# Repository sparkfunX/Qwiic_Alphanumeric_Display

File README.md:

SparkX Qwiic Alphanumeric Display
========================================

[*Alphanumeric Display (Qwiic) (SPX-)*]()

The SparkFun Qwiic Alphanumeric Display is a 14-segment, 4 digit alphanumeric display with the Holtek HT16K33 LED Driver that allows you for control every segment individually through an I2C bus. 

Repository Contents
-------------------

* **/Documents** - Data sheet for the LED Driver and Alphanumeric Displays (Blue and Red)
* **/Hardware** - Eagle design files (.brd, .sch)
* **/Production** - Production panel files (.brd) within the Production folder

License Information
-------------------

This product is _**open source**_! 

Please review the LICENSE.md file for license information. 

If you have any questions or concerns on licensing, please contact technical support on our [SparkFun forums](https://forum.sparkfun.com/viewforum.php?f=152).

Distributed as-is; no warranty is given.

- Your friends at SparkFun.

_<COLLABORATION CREDIT>_

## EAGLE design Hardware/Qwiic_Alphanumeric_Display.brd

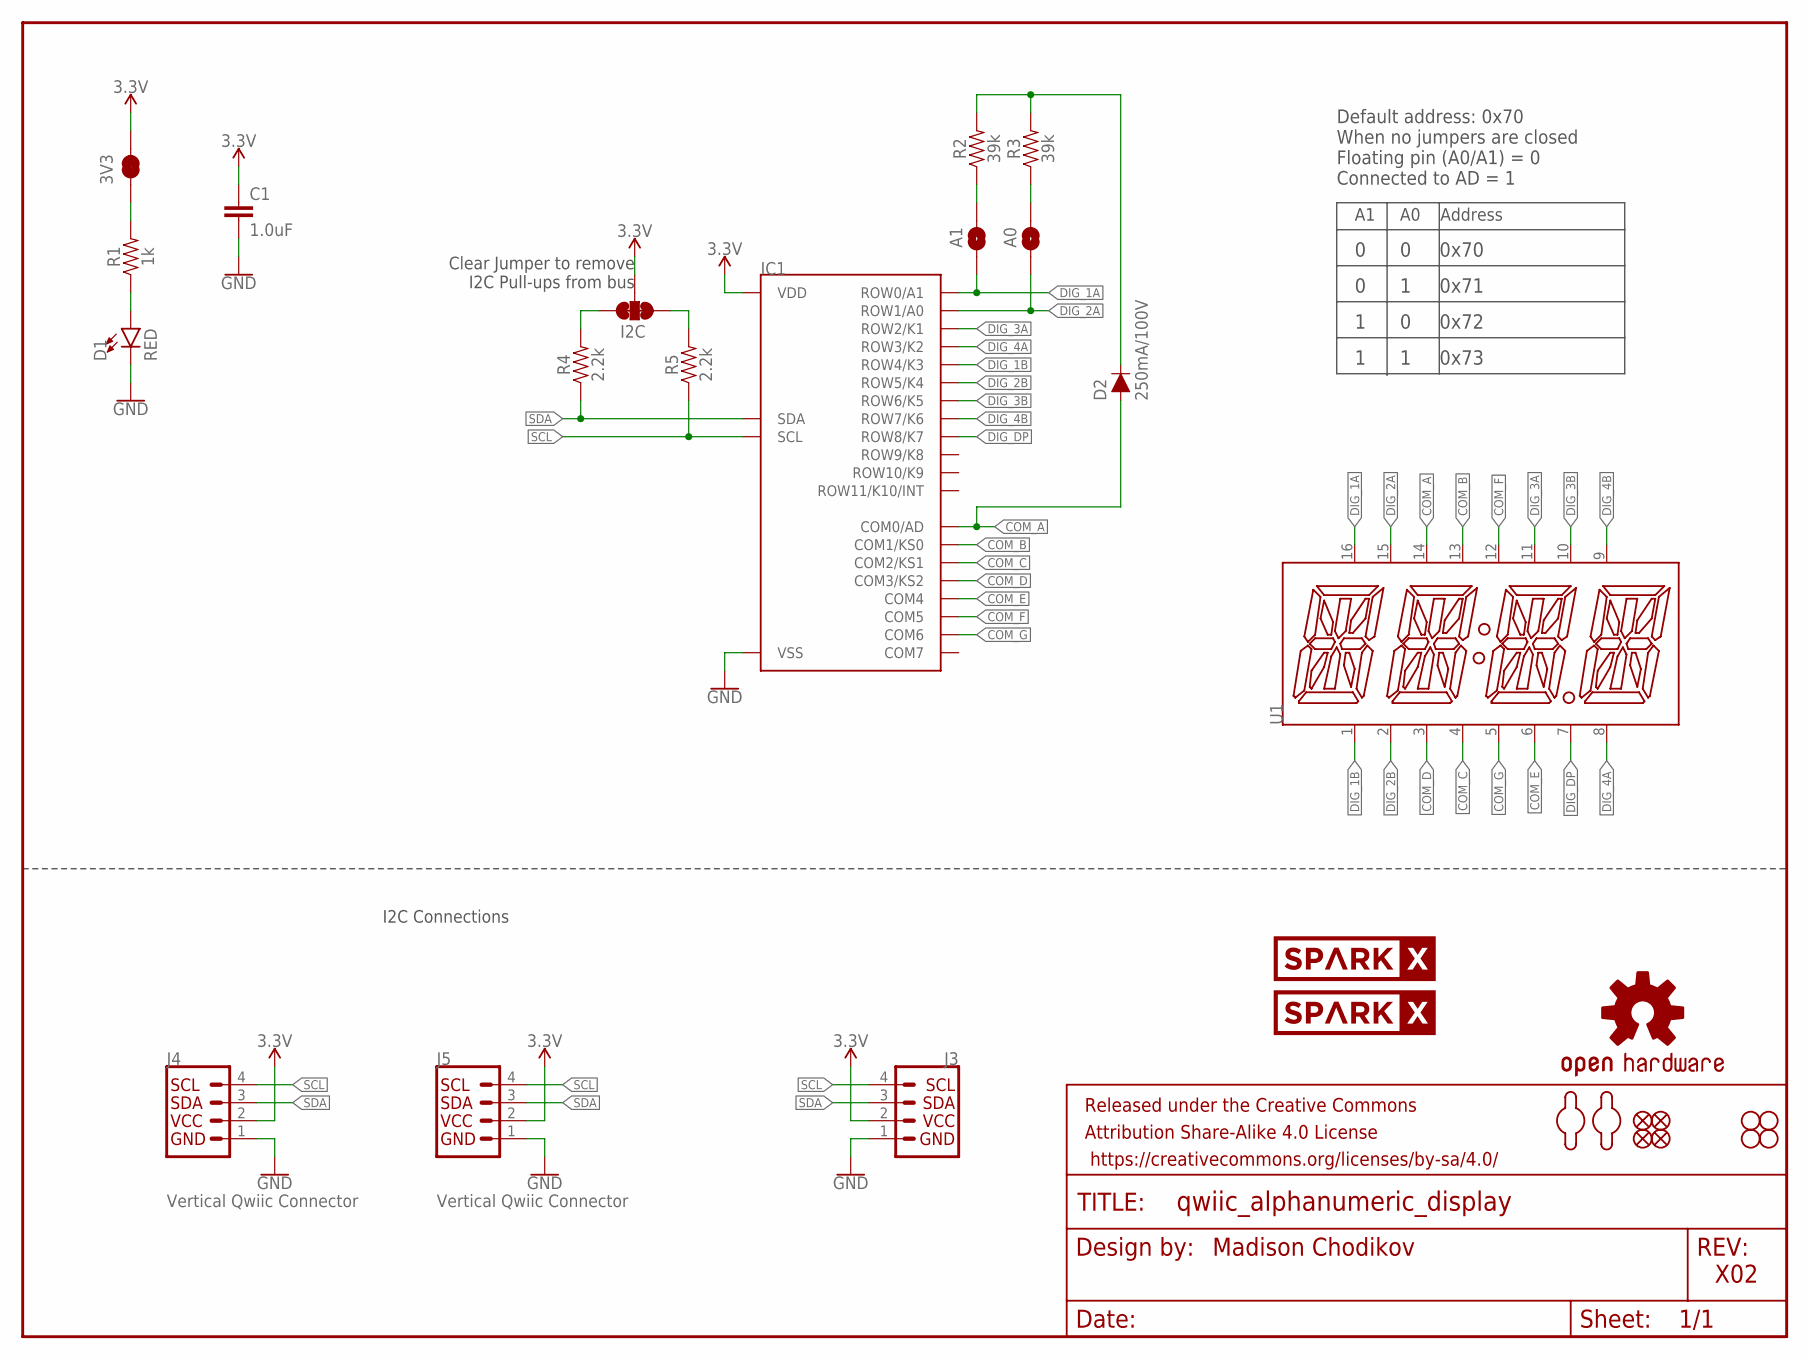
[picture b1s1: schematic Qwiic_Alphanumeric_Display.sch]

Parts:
3V3: JUMPER-SMT_2_NC_TRACE_SILK; SMT-JUMPER_2_NC_TRACE_SILK
A0, A1: JUMPER-SMT_2_NO_SILK; SMT-JUMPER_2_NO_SILK
C1: 1.0uF; 0603
D1: RED; LED-0603
D2: 250mA/100V; SOD-323
FD1, FD2, FD3, FD4: FIDUCIAL1X2; FIDUCIAL-1X2
FRAME1: FRAME-LETTER; CREATIVE_COMMONS
H1, H2, H3, H4: STAND-OFF
I2C: JUMPER-SMT_3_2-NC_TRACE_SILK; SMT-JUMPER_3_2-NC_TRACE_SILK
IC1: HT16K33
J3: I2C_STANDARD_NO_SILK; 1X04_NO_SILK
J4, J5: Vertical Qwiic Connector; JST04_1MM_VERT
LOGO1: OSHW-LOGOMINI; OSHW-LOGO-MINI
R1: 1k; 0603
R2, R3: 39k; 0603
R4, R5: 2.2k; 0603
U1: SILSMART_DISPLAY
U$7, U$8: SPARKX-LOGO4; SPARKX-MEDIUM
U$18, U$19: MOUNTING_HOLE_M2-0.4X6

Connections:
3.3V: 3V3.2, C1.1, I2C.2, IC1.24 (VDD), J3.2, J4.2, J5.2
COM_A: D2.A, IC1.2 (COM0/AD), U1.14 (COM_A)
COM_B: IC1.3 (COM1/KS0), U1.13 (COM_B)
COM_C: IC1.4 (COM2/KS1), U1.4 (COM_C)
COM_D: IC1.5 (COM3/KS2), U1.3 (COM_D)
COM_E: IC1.6 (COM4), U1.6 (COM_E)
COM_F: IC1.7 (COM5), U1.12 (COM_F)
COM_G: IC1.8 (COM6), U1.5 (COM_G1)
DIG_1A: A1.1, IC1.21 (ROW0/A1), U1.16 (DIG_1A)
DIG_1B: IC1.17 (ROW4/K3), U1.1 (DIG_1B)
DIG_2A: A0.1, IC1.20 (ROW1/A0), U1.15 (DIG_2A)
DIG_2B: IC1.16 (ROW5/K4), U1.2 (DIG_2B)
DIG_3A: IC1.19 (ROW2/K1), U1.11 (DIG_3A)
DIG_3B: IC1.15 (ROW6/K5), U1.10 (DIG_3B)
DIG_4A: IC1.18 (ROW3/K2), U1.8 (DIG_4A)
DIG_4B: IC1.14 (ROW7/K6), U1.9 (DIG_4B)
DIG_DP: IC1.13 (ROW8/K7), U1.7 (DIG_DP)
GND: C1.2, D1.C, IC1.1 (VSS), J3.1, J4.1, J5.1
unnamed: D1.A, R1.1
unnamed: A1.2, R2.1
unnamed: A0.2, R3.1
unnamed: I2C.1, R5.2
unnamed: I2C.3, R4.2
unnamed: D2.C, R2.2, R3.2
unnamed: 3V3.1, R1.2
SCL: IC1.22 (SCL), J3.4, J4.4, J5.4, R5.1
SDA: IC1.23 (SDA), J3.3, J4.3, J5.3, R4.1

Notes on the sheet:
Madison Chodikov
I2C Connections
Clear Jumper to remove I2C Pull-ups from bus
A1 A0 Address
0 0 0x70
0 1 0x71
1 0 0x72
1 1 0x73
Default address: 0x70 When no jumpers are closed Floating pin (A0/A1) = 0 Connected to AD = 1
X02

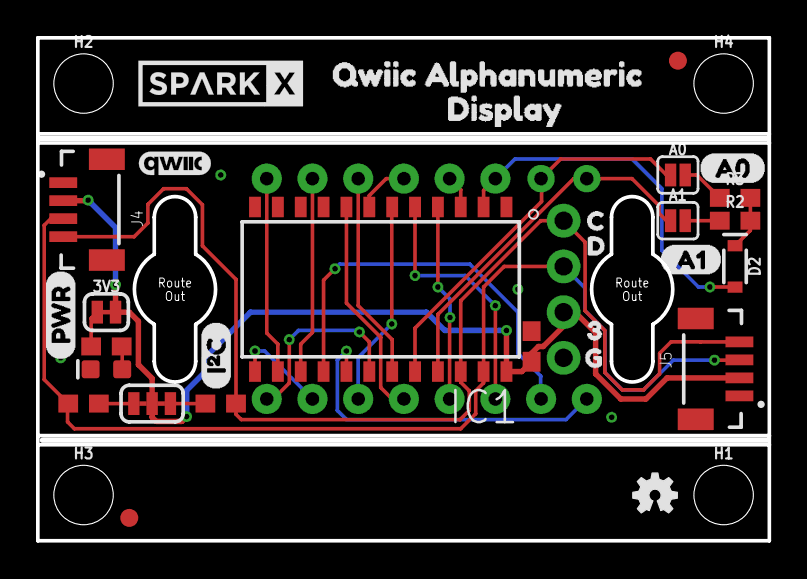
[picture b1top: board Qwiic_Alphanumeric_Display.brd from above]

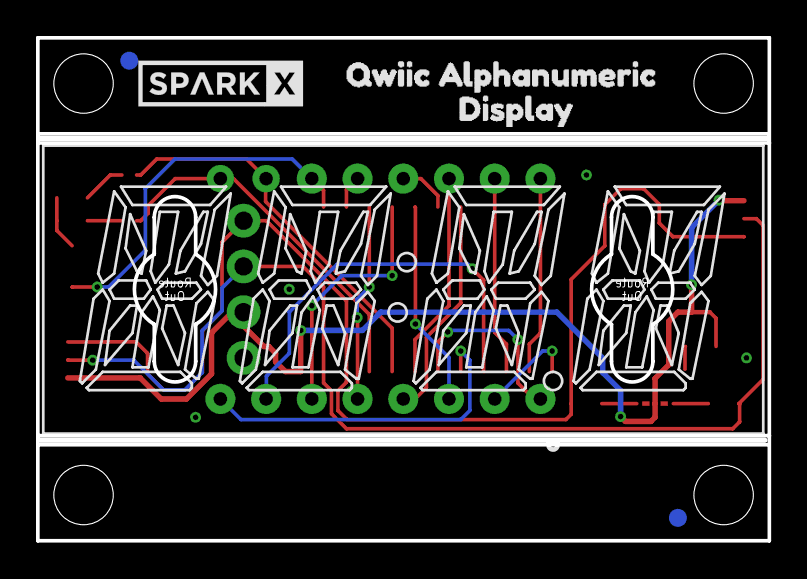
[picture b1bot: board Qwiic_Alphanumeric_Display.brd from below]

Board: 2 copper layers, 40.6 x 27.9 mm, 44 parts (6 on the bottom side), 27 nets.

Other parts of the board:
U$1: 32
U$2: C0
U$3: PWR5
U$4: D1
U$5: G3
U$6: QWIIC_4MM
U$10: I_SUPER2_C-()-04
U$13, U$15: QWIIC_ALPHANUMERIC0
U$16, U$17: DISPLAY1
U$20: A00
U$21: A11

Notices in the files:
parts and their libraries:
SparkFun-Capacitors: Licensing: Creative Commons ShareAlike 4.0 International - https://creativecommons.org/licenses/by-sa/4.0
SparkFun-Aesthetics: Released under the Creative Commons Attribution Share-Alike 4.0 License
SparkFun-Aesthetics: https://creativecommons.org/licenses/by-sa/4.0
